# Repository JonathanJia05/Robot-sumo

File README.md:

Using OpenAI Gymnasium and Pygame with TensorFlow to test and create robot control strategies for Japanese Robot Sumo matches. Implementing reinforcement learning so the robot can have dynamic strategies in response to opponent movement (as opposed to hard coded strategies).

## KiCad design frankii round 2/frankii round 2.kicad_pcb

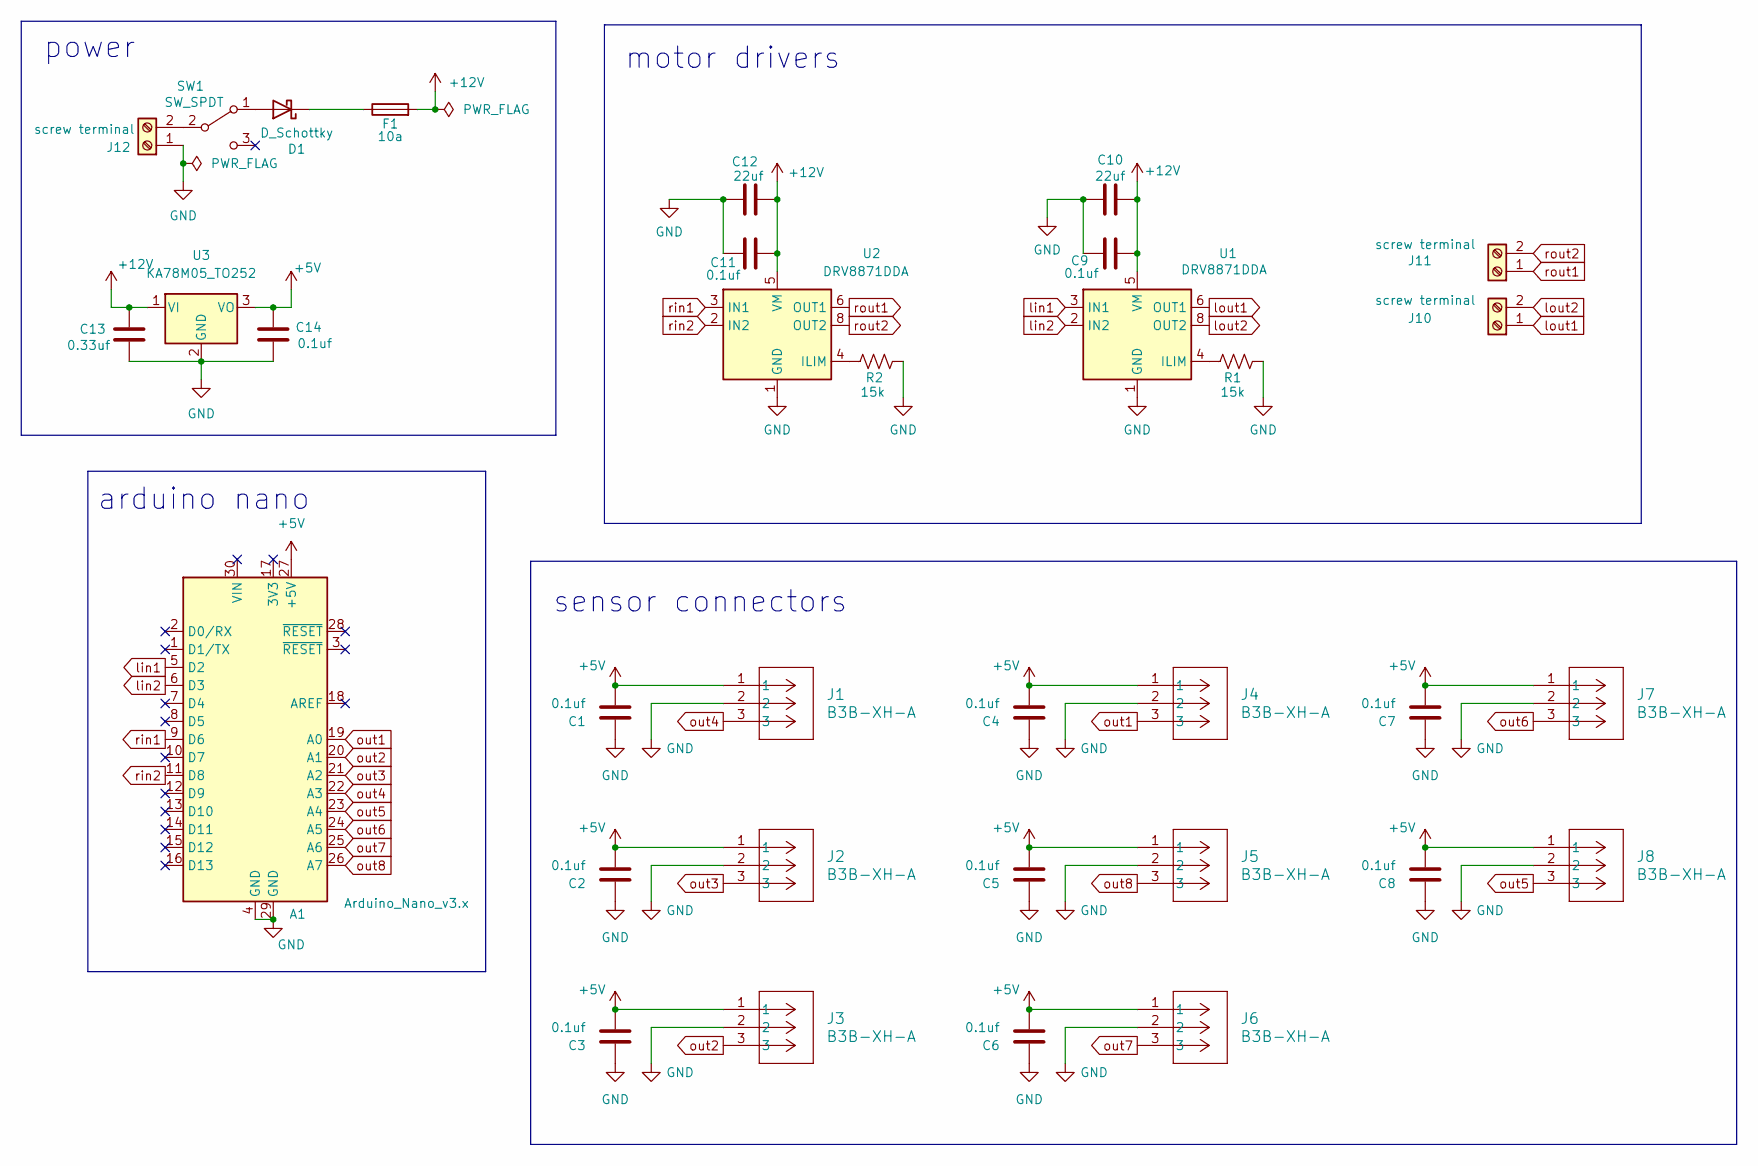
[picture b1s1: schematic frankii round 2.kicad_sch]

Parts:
A1: Arduino_Nano_v3.x; Arduino_Nano_WithMountingHoles
C1, C2, C3, C4, C5, C6, C7, C8, C9, C11, C14: 0.1uf; C_0603_1608Metric_Pad1.08x0.95mm_HandSolder
C10, C12: 22uf; CAP_EEFK_C_PAN
C13: 0.33uf; C_0805_2012Metric
D1: D_Schottky; D_SMB-SMC_Universal_Handsoldering
F1: 10a; Fuse_1206_3216Metric
J1, J2, J3, J4, J5, J6, J7, J8: B3B-XH-A; CONN_B3B-XH-A_JST
J10, J11, J12: screw terminal; TerminalBlock_4Ucon_1x02_P3.50mm_Horizontal
R1, R2: 15k; R_0805_2012Metric
SW1: SW_SPDT; SPDT_OS102011_CNK
U1, U2: DRV8871DDA; Texas_HTSOP-8-1EP_3.9x4.9mm_P1.27mm_EP2.95x4.9mm_Mask2.4x3.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
U3: KA78M05_TO252; TO-252-3_TabPin2

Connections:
+5V: A1.27 (+5V), C1.2, C2.2, C3.2, C4.2, C5.2, C6.2, C7.2, C8.2, C14.1, J1.1, J2.1, J3.1, J4.1, J5.1, J6.1, J7.1, J8.1, U3.3 (VO)
+12V: C9.1, C10.1, C11.1, C12.1, C13.1, F1.2, U1.5 (VM), U2.5 (VM), U3.1 (VI)
GND: A1.4 (GND), A1.29 (GND), C1.1, C2.1, C3.1, C4.1, C5.1, C6.1, C7.1, C8.1, C9.2, C10.2, C11.2, C12.2, C13.2, C14.2, J1.2, J2.2, J3.2, J4.2, J5.2, J6.2, J7.2, J8.2, J12.1, R1.1, R2.2, U1.1 (GND), U1.7 (GND), U1.9 (GND), U2.1 (GND), U2.7 (GND), U2.9 (GND), U3.2 (GND)
unnamed: D1.2 (A), SW1.1 (A)
unnamed: D1.1 (K), F1.1
unnamed: J12.2, SW1.2 (B)
unnamed: R1.2, U1.4 (ILIM)
unnamed: R2.1, U2.4 (ILIM)
lin1: A1.5 (D2), U1.3 (IN1)
lin2: A1.6 (D3), U1.2 (IN2)
lout1: J10.1, U1.6 (OUT1)
lout2: J10.2, U1.8 (OUT2)
out1: A1.19 (A0), J4.3
out2: A1.20 (A1), J3.3
out3: A1.21 (A2), J2.3
out4: A1.22 (A3), J1.3
out5: A1.23 (A4), J8.3
out6: A1.24 (A5), J7.3
out7: A1.25 (A6), J6.3
out8: A1.26 (A7), J5.3
rin1: A1.9 (D6), U2.3 (IN1)
rin2: A1.11 (D8), U2.2 (IN2)
rout1: J11.1, U2.6 (OUT1)
rout2: J11.2, U2.8 (OUT2)

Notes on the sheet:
power
arduino nano
motor drivers
sensor connectors

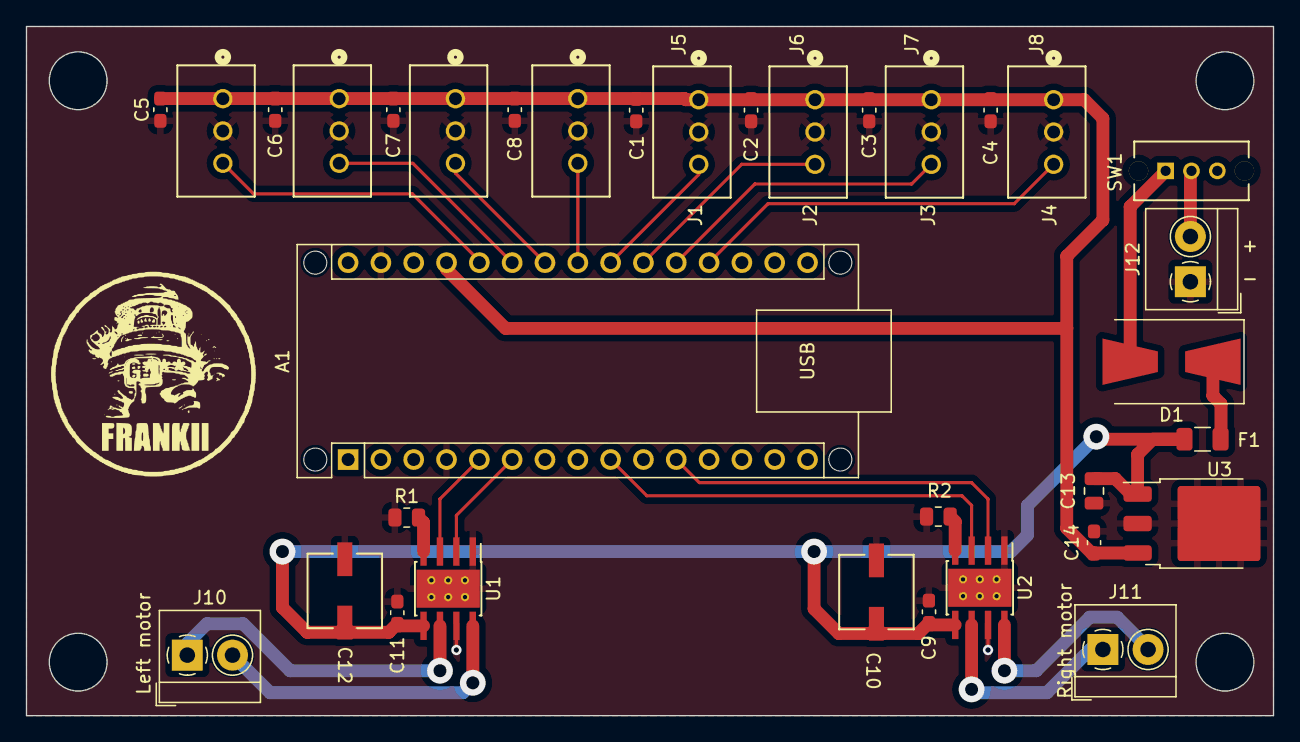
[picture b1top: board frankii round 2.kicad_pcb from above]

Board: 2 copper layers, 96.5 x 53.3 mm, 34 parts (0 on the bottom side), 24 nets.

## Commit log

2024-09-18 Added kicad files
    Designed pcb, added files
2024-09-18 Designed pcb, added kicad files to repository
2024-09-18 Added pcb and 3d file
2024-09-19 made new python project
2024-09-19 created a 2dbox environment, tested basic functionality of robot
2024-09-20 made movement of robot and opponent more realistic
2024-09-20 renamed project,made movement of bot and opponent more realistic
2024-10-05 incorporated tensorflow, set up initial structure for DQN agent
